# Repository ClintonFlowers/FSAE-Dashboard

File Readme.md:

# KSU Motorsports Dashboard & Data Logger

This is a custom dashboard / shift-light module created for the Kennesaw State University Motorsports student-built race car, the KS-2.
In a 5" x 1.25" x 0.5" footprint, it has:

* 20 individually-addressable RGB LED's (Neopixels)
* 3 14-segment alphanumeric LED elements for string output via scrolling text
* CAN bus communication with solderable termination jumper
* Onboard 12V to 5V switching converter plus overvoltage, transient, overcurrent, and reverse-voltage protection (i.e., Partially Student Resistant)
* A 9-DOF (accelerometer/gyro/magnetometer) inertial measurement unit with integrated sensor fusion
* A battery-backed Realtime Clock
* A Micro SD Card slot
* A 5-way Tactile Switch/Joystick
* Expansion capability via a 0.1" header at the bottom left, designed for a 16x2 character matrix or any I2C device

It's based on a combination of a Atmega328P (Arduino Uno) and a Atmega2560 (Arduino Mega) to ensure team members can program it into the future.

I've included a PDF to view the schematic without EagleCAD, and the models (STL/SLDPRT) of the enclosure pieces. The version 1 faceplate and backplate were designed for Formlabs clear resin, as the backplate's integrated cable-tie strain-relief loops may break more easily on FDM prints (due to Z-axis layer adhesion). Newer designs (version 2+) use a thin waterjet polycarbonate faceplate for simplicity.

Feel free to contact me with any questions,

Clinton Flowers

clintonflowers222@gmail.com

   Copyright 2017 Clinton Flowers

   Licensed under the Apache License, Version 2.0 (the "License");
   you may not use this file except in compliance with the License.
   You may obtain a copy of the License at

       http://www.apache.org/licenses/LICENSE-2.0

   Unless required by applicable law or agreed to in writing, software
   distributed under the License is distributed on an "AS IS" BASIS,
   WITHOUT WARRANTIES OR CONDITIONS OF ANY KIND, either express or implied.
   See the License for the specific language governing permissions and
   limitations under the License.

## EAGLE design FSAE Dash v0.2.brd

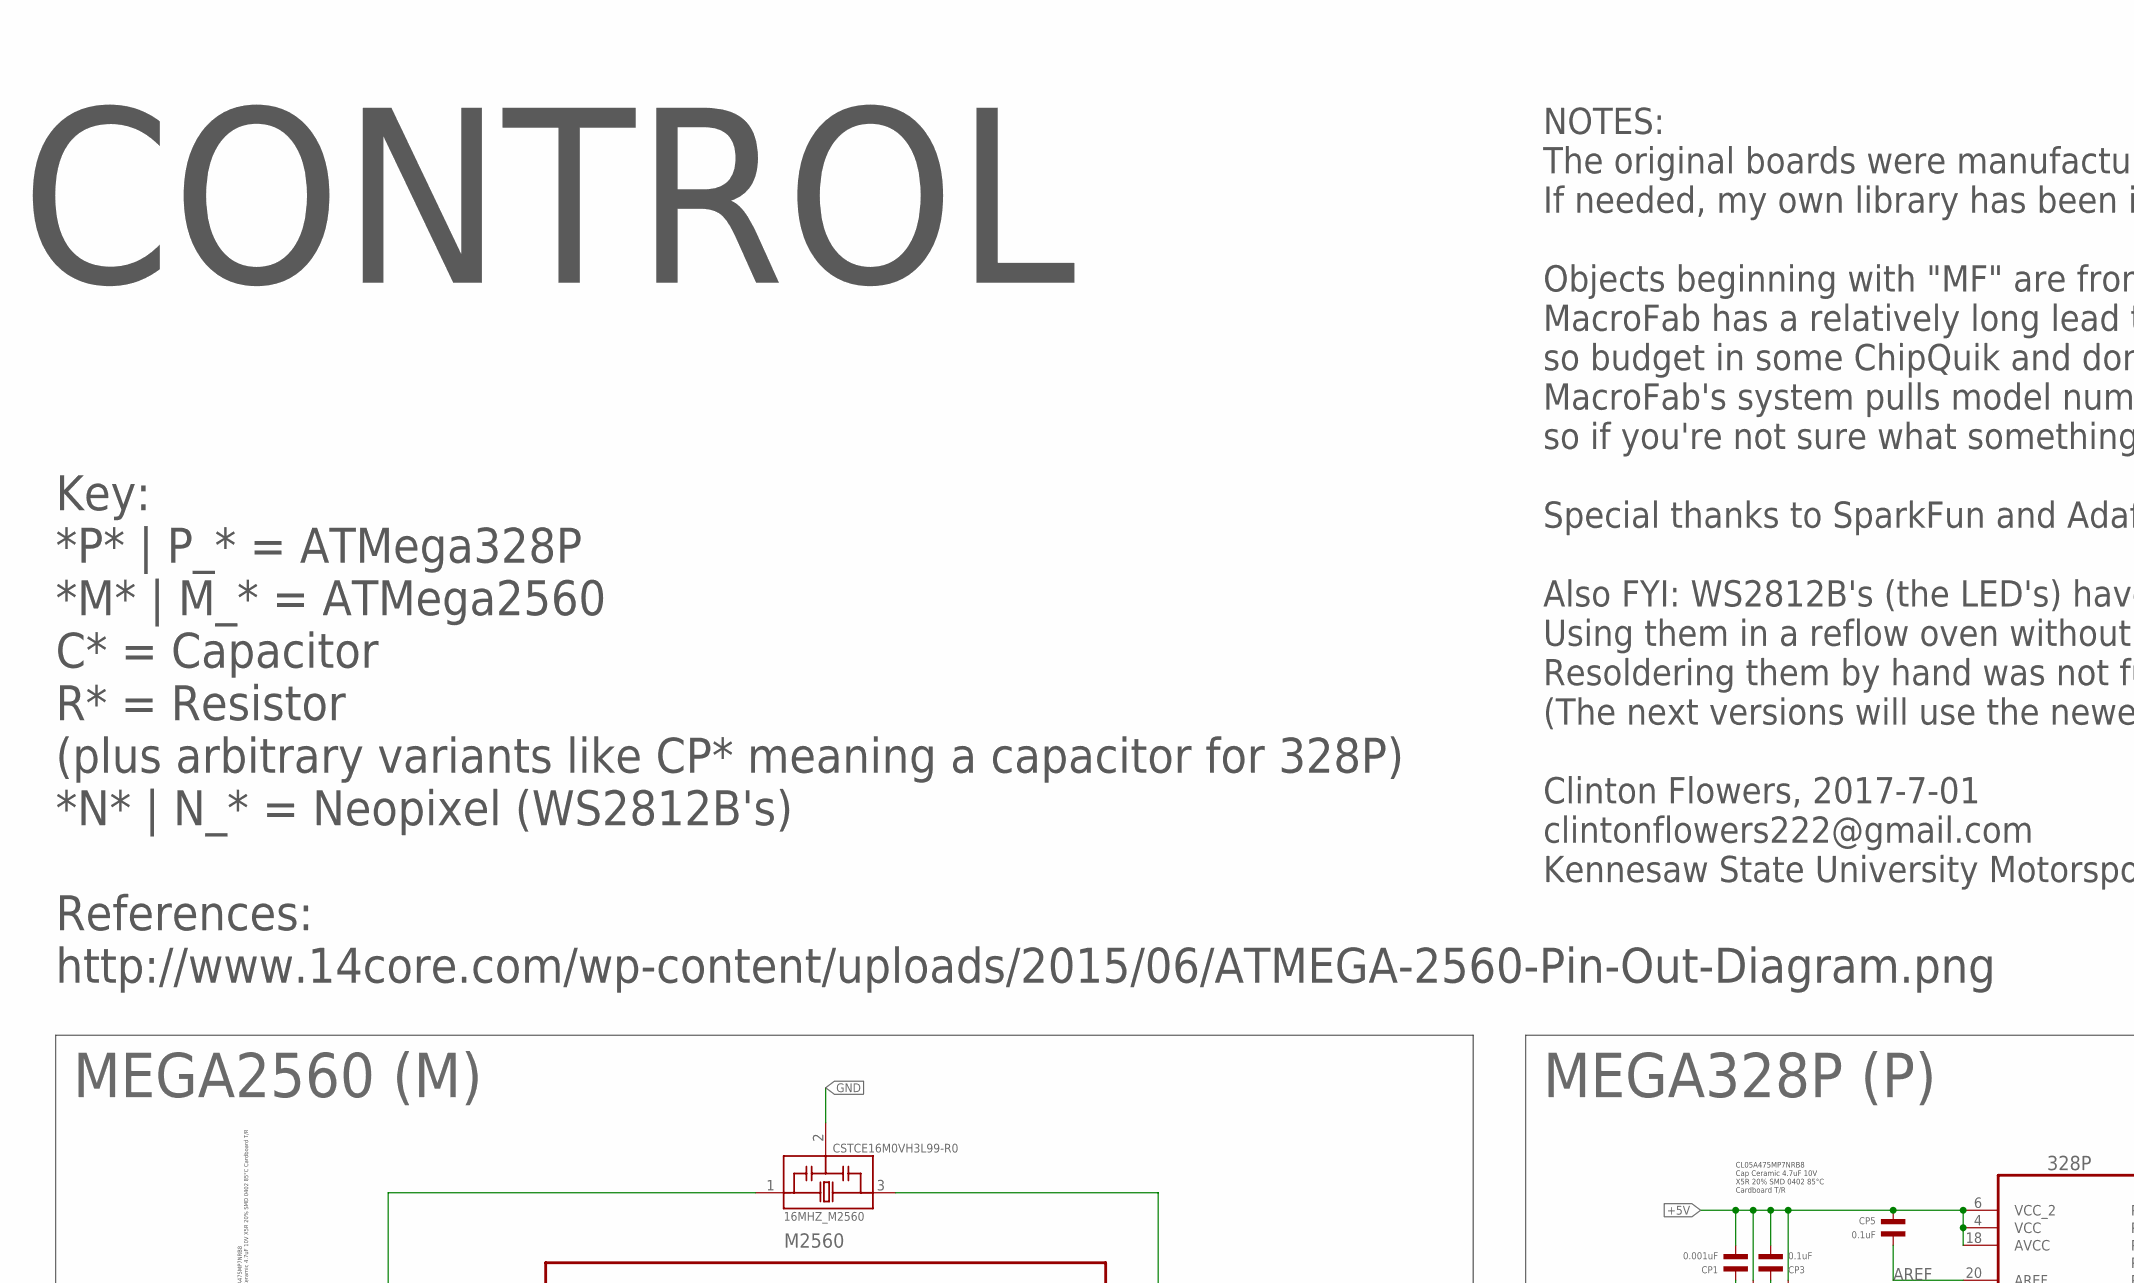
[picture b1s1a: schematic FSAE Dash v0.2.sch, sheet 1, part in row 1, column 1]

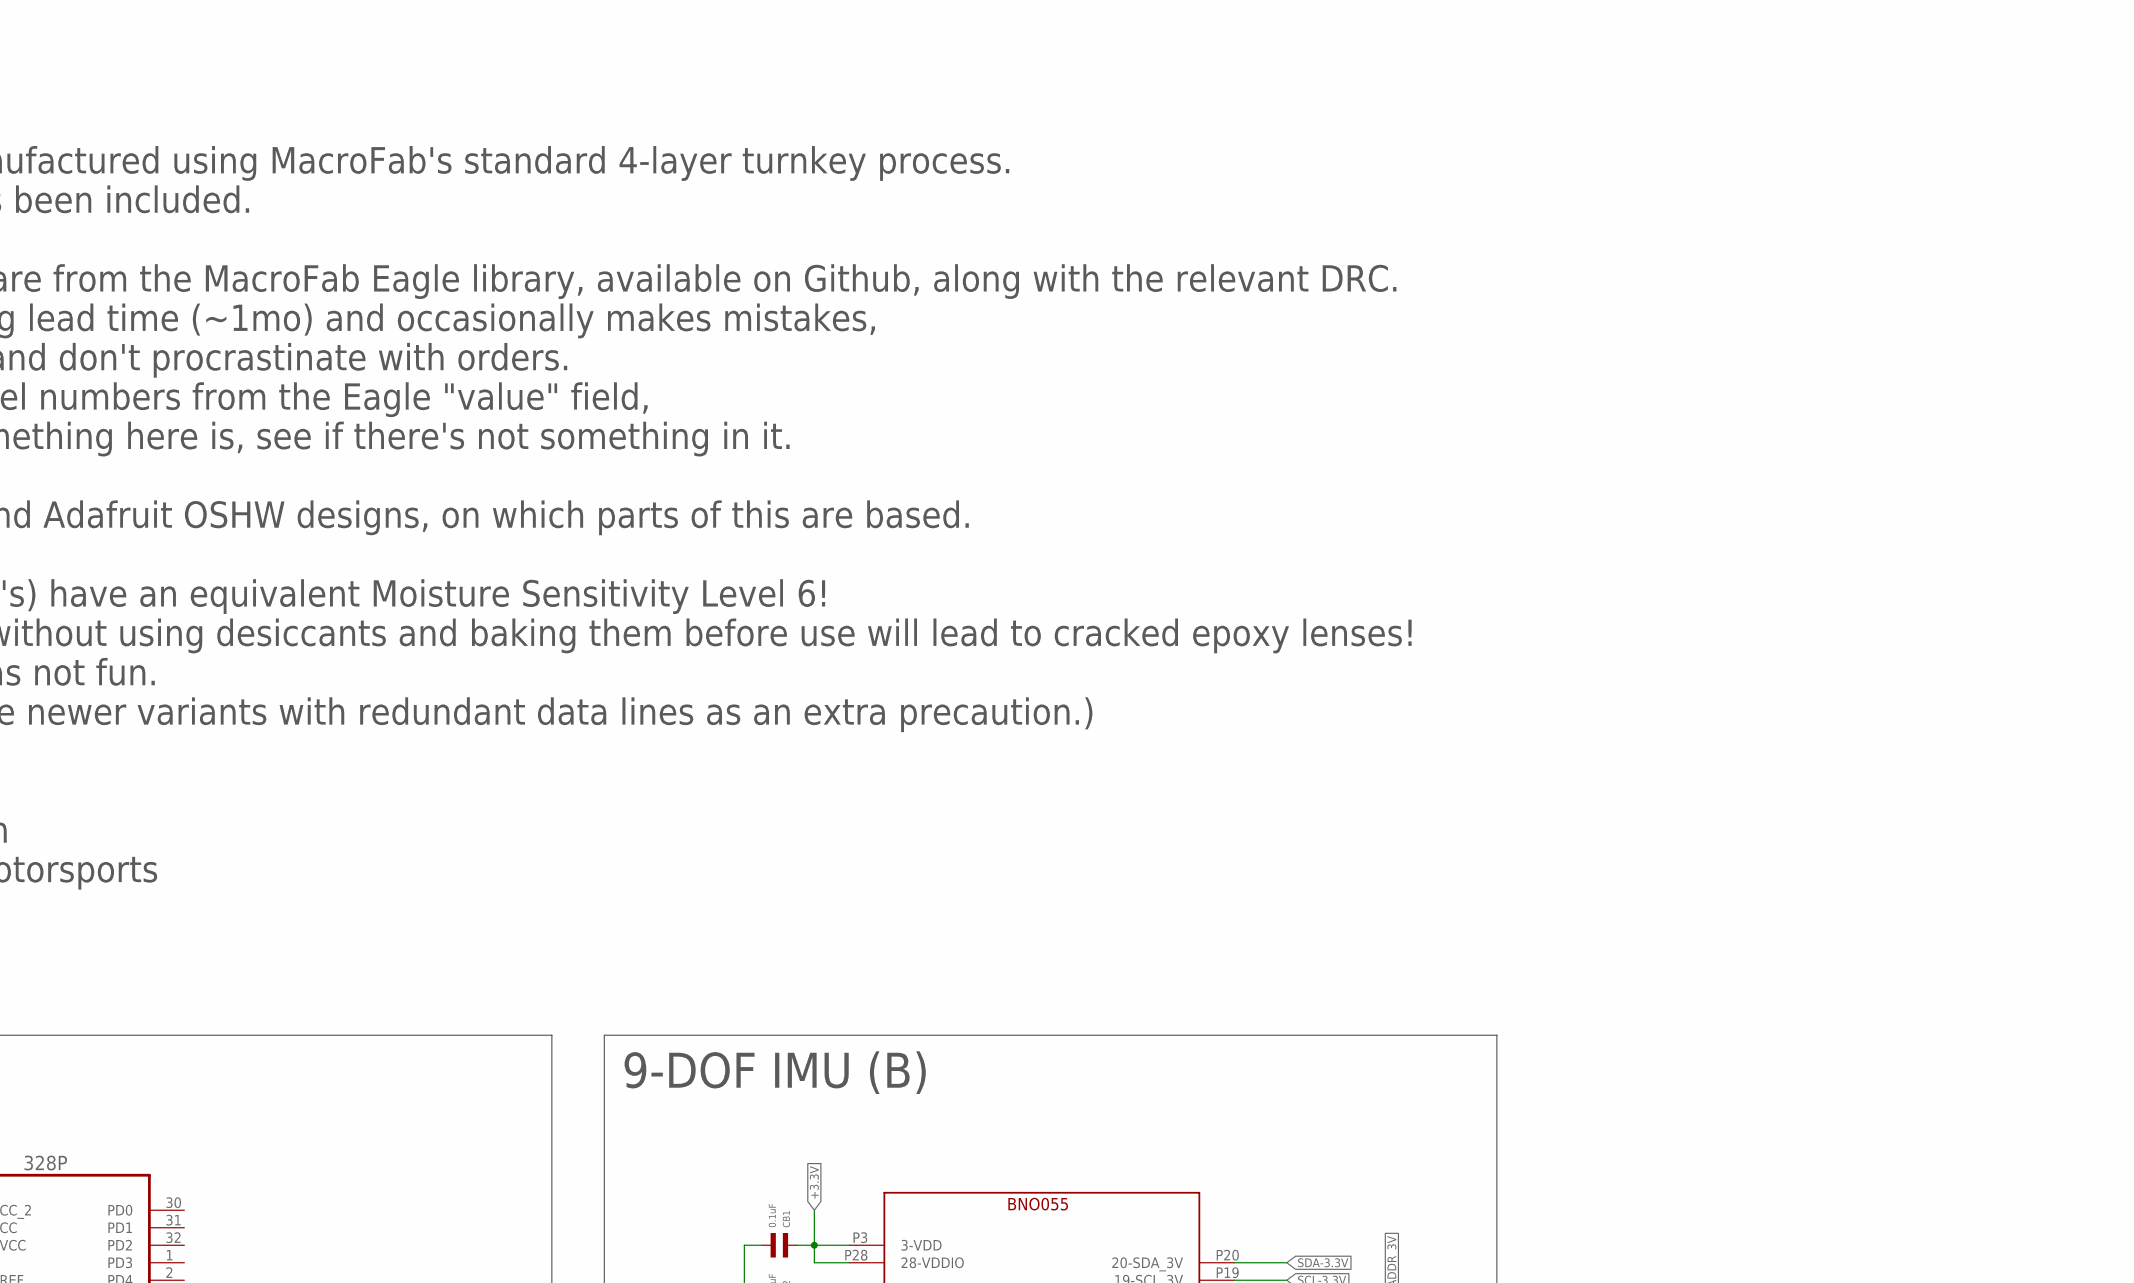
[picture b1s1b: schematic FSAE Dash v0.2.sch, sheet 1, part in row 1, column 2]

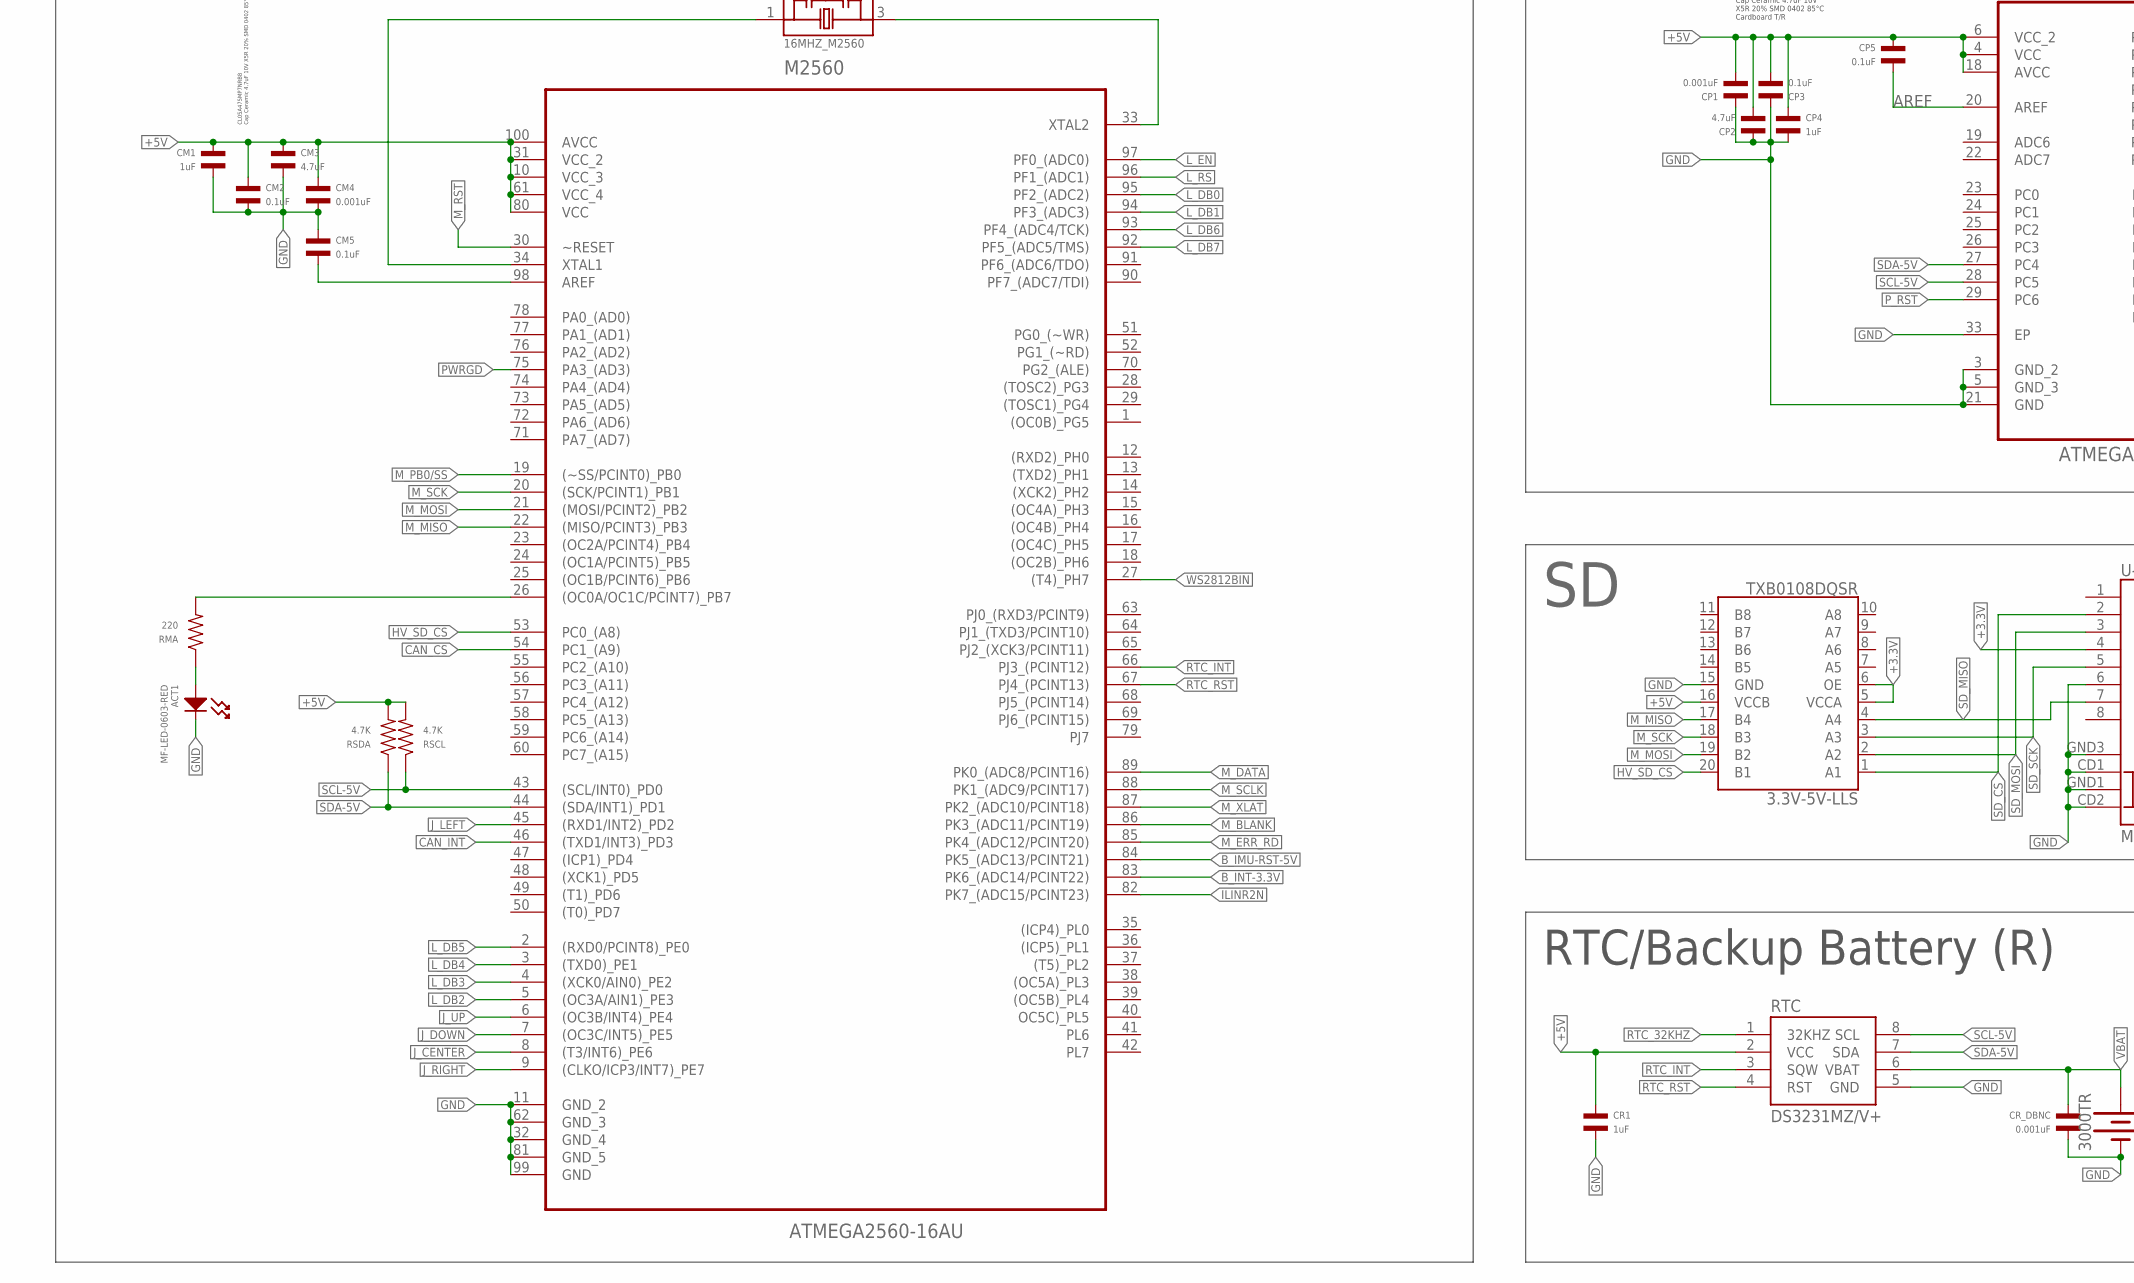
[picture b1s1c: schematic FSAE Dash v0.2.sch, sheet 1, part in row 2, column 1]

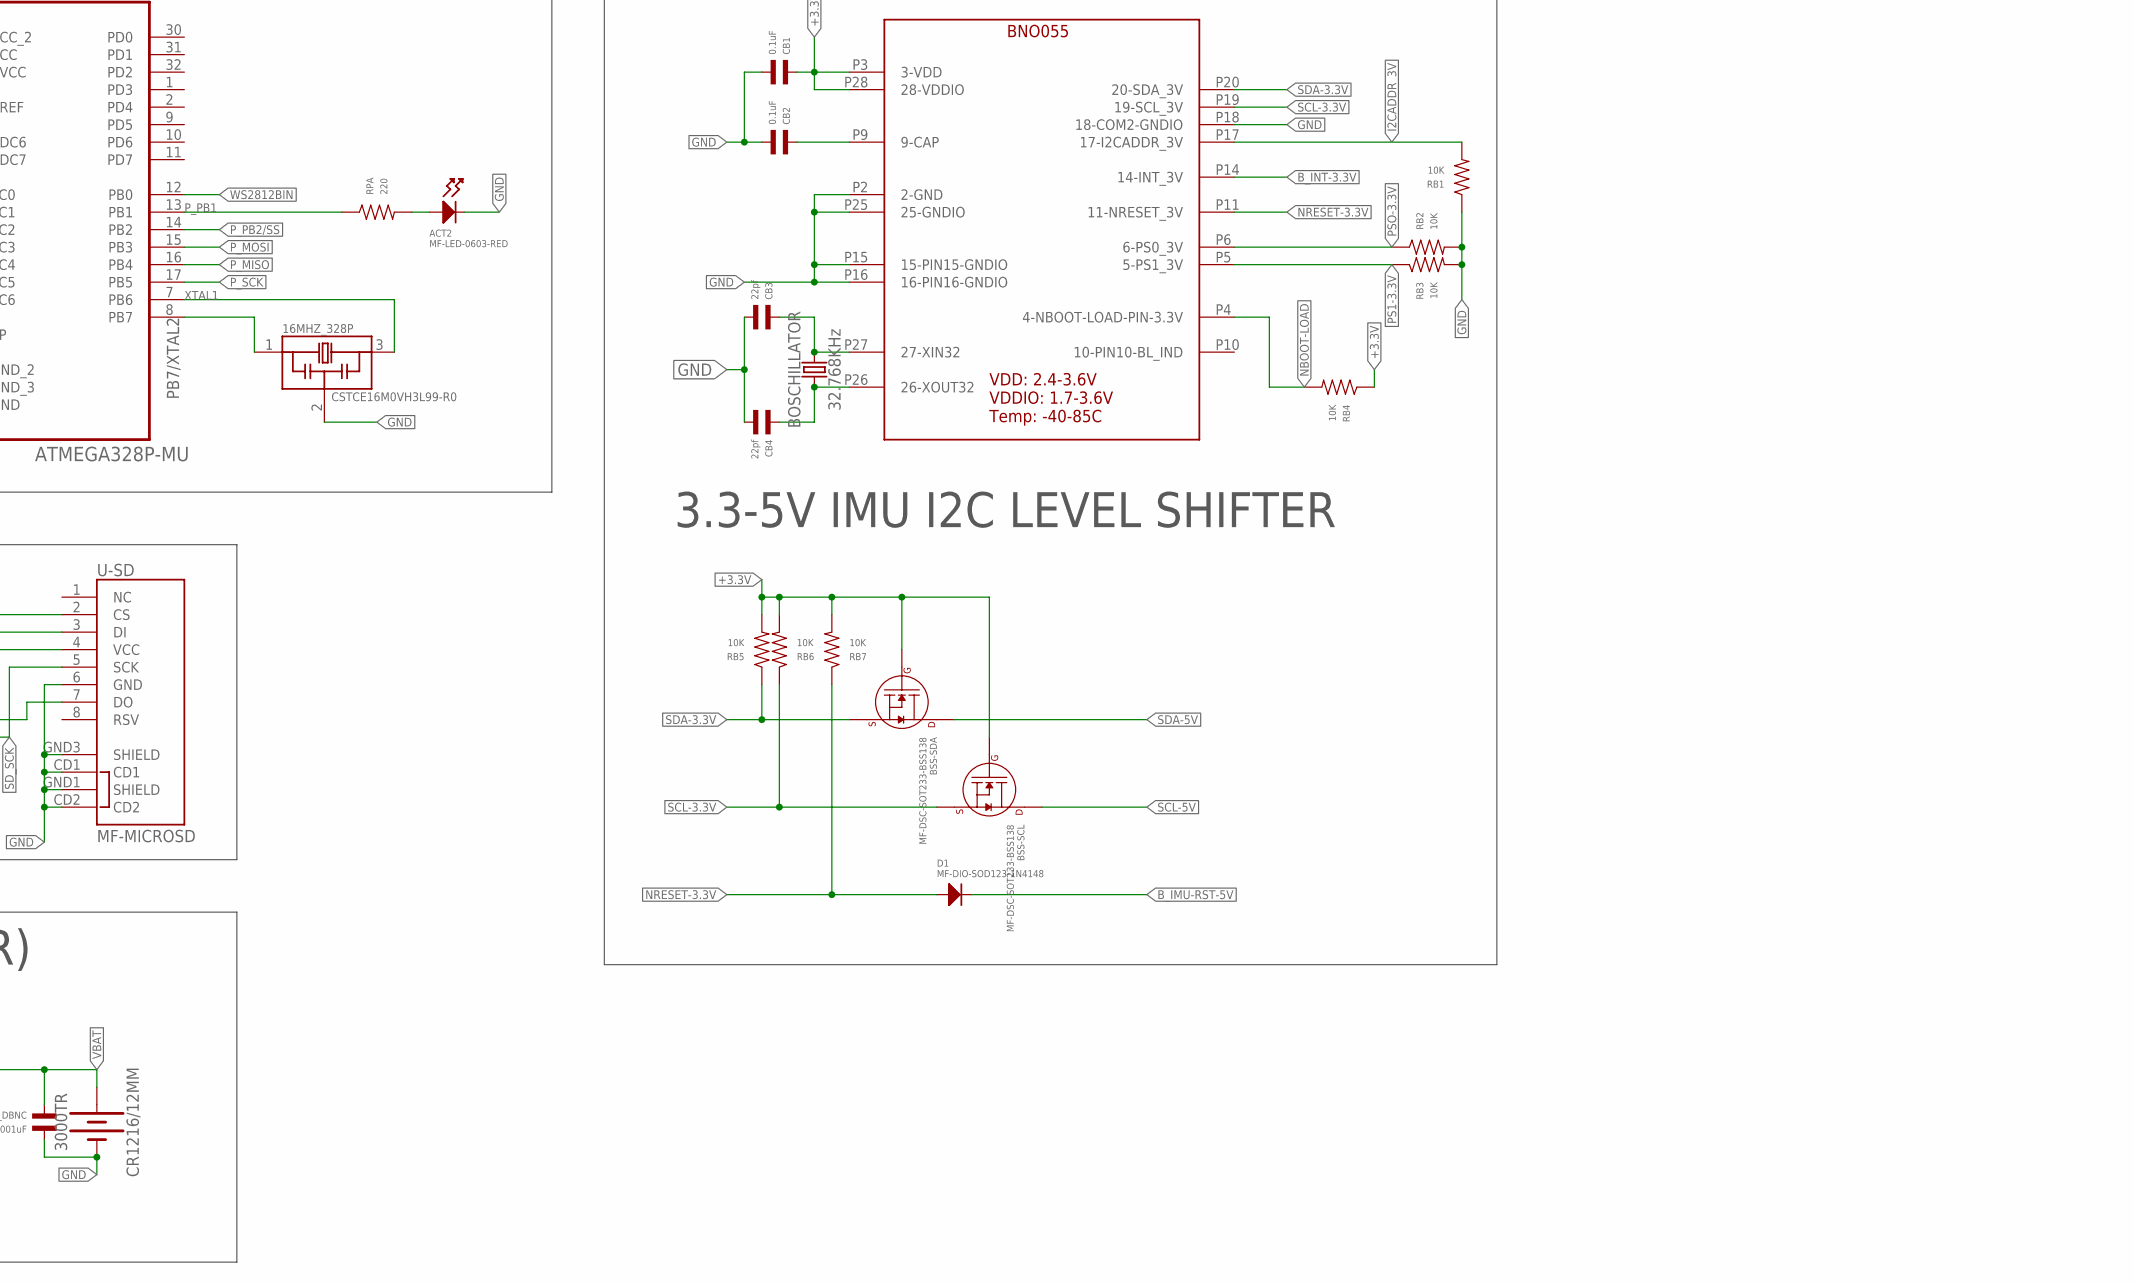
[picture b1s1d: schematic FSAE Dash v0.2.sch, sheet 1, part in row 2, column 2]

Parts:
3.3V-5V-LLS: TXB0108DQSR; UFDFN-20
16MHZ_328P, 16MHZ_M2560: CSTCE16M0VH3L99-R0; OSC_CSTCE16M0V53-R0
328P: ATMEGA328P-MU; QFN50P500X500X100-33N
ACT1, ACT2: MF-LED-0603-RED; LED0603
BNO: BNO055; BOSCH-BNO055
BOSCHILLATOR: 32.768KHz; CRYSTAL-SMD-3.2X1.5MM
BSS-SCL: MF-DSC-SOT233-BSS138; SOT-23-3
BSS-SDA: MF-DSC-SOT233-BSS138; SOT-23-3
CB1, CB2: 0.1uF; C0402
CB3, CB4: 22pf; C0402
CM1: 1uF; C0402
CM2, CM5: 0.1uF; C0402
CM3: 4.7uF; C0402
CM4: 0.001uF; C0402
CP1: 0.001uF; C0402
CP2: 4.7uF; C0402
CP3, CP5: 0.1uF; C0402
CP4: 1uF; C0402
CR1: 1uF; C0402
CR1216/12MM: 3000TR; BATTCON_12MM
CR_DBNC: 0.001uF; C0402
D1: MF-DIO-SOD123-1N4148; SOD-123
M2560: ATMEGA2560-16AU; QFP50P1600X1600X120-100N
RB1, RB2, RB3, RB4, RB5, RB6, RB7: 10K; R0402
RMA: 220; R0402
RPA: 220; R0402
RSCL: 4.7K; R0402
RSDA: 4.7K; R0402
RTC: DS3231MZ/V+; SO08
U-SD: MF-MICROSD; MICROSD_1:1

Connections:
+3.3V: 3.3V-5V-LLS.5 (VCCA), 3.3V-5V-LLS.6 (OE), BNO.P3 (3-VDD), BNO.P28 (28-VDDIO), BSS-SCL.P$1 (GATE), BSS-SDA.P$1 (GATE), CB1.P$1, RB4.P$1, RB5.P$2, RB6.P$2, RB7.P$2, U-SD.4 (VCC); also elsewhere on the board
+5V: 3.3V-5V-LLS.16 (VCCB), 328P.4 (VCC), 328P.6 (VCC_2), 328P.18 (AVCC), CM1.P$1, CM2.P$1, CM3.P$1, CM4.P$1, CP1.P$2, CP2.P$2, CP3.P$2, CP4.P$1, CP5.P$1, CR1.P$1, M2560.10 (VCC_3), M2560.31 (VCC_2), M2560.61 (VCC_4), M2560.80 (VCC), M2560.100 (AVCC), RSCL.P$2, RSDA.P$2, RTC.2 (VCC); also elsewhere on the board
AREF: 328P.20 (AREF), CP5.P$2
BCAP: BNO.P9 (9-CAP), CB2.P$1
B_IMU-RST-5V: D1.CATHODE, M2560.84 (PK5_(ADC13/PCINT21))
B_INT-3.3V: BNO.P14 (14-INT_3V), M2560.83 (PK6_(ADC14/PCINT22))
CAN_CS: M2560.54 (PC1_(A9)); also elsewhere on the board
CAN_INT: M2560.46 ((TXD1/INT3)_PD3); also elsewhere on the board
GND: 3.3V-5V-LLS.15 (GND), 16MHZ_328P.2, 16MHZ_M2560.2, 328P.3 (GND_2), 328P.5 (GND_3), 328P.21 (GND), 328P.33 (EP), ACT1.CATHODE, ACT2.CATHODE, BNO.P2 (2-GND), BNO.P15 (15-PIN15-GNDIO), BNO.P16 (16-PIN16-GNDIO), BNO.P18 (18-COM2-GNDIO), BNO.P25 (25-GNDIO), CB1.P$2, CB2.P$2, CB3.P$2, CB4.P$2, CM1.P$2, CM2.P$2, CM3.P$2, CM4.P$2, CM5.P$1, CP1.P$1, CP2.P$1, CP3.P$1, CP4.P$2, CR1.P$2, CR1216/12MM.GND (-), CR_DBNC.P$2, M2560.11 (GND_2), M2560.32 (GND_4), M2560.62 (GND_3), M2560.81 (GND_5), M2560.99 (GND), RB1.P$1, RB2.P$2, RB3.P$2, RTC.5 (GND), U-SD.6 (GND), U-SD.CD1, U-SD.CD2, U-SD.GND1 (SHIELD), U-SD.GND3 (SHIELD); also elsewhere on the board
HV_SD_CS: 3.3V-5V-LLS.20 (B1), M2560.53 (PC0_(A8))
I2CADDR_3V: BNO.P17 (17-I2CADDR_3V), RB1.P$2
ILINR2N: M2560.82 (PK7_(ADC15/PCINT23)); also elsewhere on the board
J_CENTER: M2560.8 ((T3/INT6)_PE6); also elsewhere on the board
J_DOWN: M2560.7 ((OC3C/INT5)_PE5); also elsewhere on the board
J_LEFT: M2560.45 ((RXD1/INT2)_PD2); also elsewhere on the board
J_RIGHT: M2560.9 ((CLKO/ICP3/INT7)_PE7); also elsewhere on the board
J_UP: M2560.6 ((OC3B/INT4)_PE4); also elsewhere on the board
L_DB0: M2560.95 (PF2_(ADC2)); also elsewhere on the board
L_DB1: M2560.94 (PF3_(ADC3)); also elsewhere on the board
L_DB2: M2560.5 ((OC3A/AIN1)_PE3); also elsewhere on the board
L_DB3: M2560.4 ((XCK0/AIN0)_PE2); also elsewhere on the board
L_DB4: M2560.3 ((TXD0)_PE1); also elsewhere on the board
L_DB5: M2560.2 ((RXD0/PCINT8)_PE0); also elsewhere on the board
L_DB6: M2560.93 (PF4_(ADC4/TCK)); also elsewhere on the board
L_DB7: M2560.92 (PF5_(ADC5/TMS)); also elsewhere on the board
L_EN: M2560.97 (PF0_(ADC0)); also elsewhere on the board
L_RS: M2560.96 (PF1_(ADC1)); also elsewhere on the board
M_BLANK: M2560.86 (PK3_(ADC11/PCINT19)); also elsewhere on the board
M_DATA: M2560.89 (PK0_(ADC8/PCINT16)); also elsewhere on the board
M_ERR_RD: M2560.85 (PK4_(ADC12/PCINT20)); also elsewhere on the board
M_MISO: 3.3V-5V-LLS.17 (B4), M2560.22 ((MISO/PCINT3)_PB3); also elsewhere on the board
M_MOSI: 3.3V-5V-LLS.19 (B2), M2560.21 ((MOSI/PCINT2)_PB2); also elsewhere on the board
M_PB0/SS: M2560.19 ((~SS/PCINT0)_PB0)
M_RST: M2560.30 (~RESET); also elsewhere on the board
M_SCK: 3.3V-5V-LLS.18 (B3), M2560.20 ((SCK/PCINT1)_PB1); also elsewhere on the board
M_SCLK: M2560.88 (PK1_(ADC9/PCINT17)); also elsewhere on the board
M_XLAT: M2560.87 (PK2_(ADC10/PCINT18)); also elsewhere on the board
unnamed: ACT2.ANODE, RPA.P$2
unnamed: 16MHZ_M2560.3, M2560.33 (XTAL2)
unnamed: CM5.P$2, M2560.98 (AREF)
unnamed: 16MHZ_M2560.1, M2560.34 (XTAL1)
unnamed: ACT1.ANODE, RMA.P$1
unnamed: BNO.P26 (26-XOUT32), BOSCHILLATOR.P$1 (1), CB4.P$1
unnamed: BNO.P27 (27-XIN32), BOSCHILLATOR.P$2 (2), CB3.P$1
unnamed: M2560.26 ((OC0A/OC1C/PCINT7)_PB7), RMA.P$2
NBOOT-LOAD: BNO.P4 (4-NBOOT-LOAD-PIN-3.3V), RB4.P$2
NRESET-3.3V: BNO.P11 (11-NRESET_3V), D1.ANODE, RB7.P$1
PB7/XTAL2: 16MHZ_328P.1, 328P.8 (PB7)
PS1-3.3V: BNO.P5 (5-PS1_3V), RB3.P$1
PSO-3.3V: BNO.P6 (6-PS0_3V), RB2.P$1
PWRGD: M2560.75 (PA3_(AD3)); also elsewhere on the board
P_MISO: 328P.16 (PB4); also elsewhere on the board
P_MOSI: 328P.15 (PB3); also elsewhere on the board
P_PB1: 328P.13 (PB1), RPA.P$1
P_PB2/SS: 328P.14 (PB2)
P_RST: 328P.29 (PC6); also elsewhere on the board
P_SCK: 328P.17 (PB5); also elsewhere on the board
RTC_32KHZ: RTC.1 (32KHZ)
RTC_INT: M2560.66 (PJ3_(PCINT12)), RTC.3 (SQW)
RTC_RST: M2560.67 (PJ4_(PCINT13)), RTC.4 (RST)
SCL-3.3V: BNO.P19 (19-SCL_3V), BSS-SCL.P$2 (SOURCE), RB6.P$1
SCL-5V: 328P.28 (PC5), BSS-SCL.P$3 (DRAIN), M2560.43 ((SCL/INT0)_PD0), RSCL.P$1, RTC.8 (SCL); also elsewhere on the board
SDA-3.3V: BNO.P20 (20-SDA_3V), BSS-SDA.P$2 (SOURCE), RB5.P$1
SDA-5V: 328P.27 (PC4), BSS-SDA.P$3 (DRAIN), M2560.44 ((SDA/INT1)_PD1), RSDA.P$1, RTC.7 (SDA); also elsewhere on the board
SD_CS: 3.3V-5V-LLS.1 (A1), U-SD.2 (CS)
SD_MISO: 3.3V-5V-LLS.4 (A4), U-SD.7 (DO)
SD_MOSI: 3.3V-5V-LLS.2 (A2), U-SD.3 (DI)
SD_SCK: 3.3V-5V-LLS.3 (A3), U-SD.5 (SCK)
VBAT: CR1216/12MM.PWR@1 (+), CR_DBNC.P$1, RTC.6 (VBAT)
WS2812BIN: 328P.12 (PB0), M2560.27 ((T4)_PH7); also elsewhere on the board
XTAL1: 16MHZ_328P.3, 328P.7 (PB6)

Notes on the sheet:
MEGA2560 (M)
MEGA328P (P)
CL05A475MP7NRB8 Cap Ceramic 4.7uF 10V X5R 20% SMD 0402 85°C Cardboard T/R
CL05A475MP7NRB8 Cap Ceramic 4.7uF 10V X5R 20% SMD 0402 85°C Cardboard T/R
Key: *P* | P_* = ATMega328P *M* | M_* = ATMega2560 C* = Capacitor R* = Resistor (plus arbitrary variants like CP* meaning a capacitor for 328P) *N* | N_* = Neopixel (WS2812B's) References: http://www.14core.com/wp-content/uploads/2015/06/ATMEGA-2560-Pin-Out-Diagram.png
CONTROL
9-DOF IMU (B)
3.3-5V IMU I2C LEVEL SHIFTER
RTC/Backup Battery (R)
NOTES: The original boards were manufactured using MacroFab's standard 4-layer turnkey process. If needed, my own library has been included. Objects beginning with "MF" are from the MacroFab Eagle library, available on Github, along with the relevant DRC. MacroFab has a relatively long lead time (~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

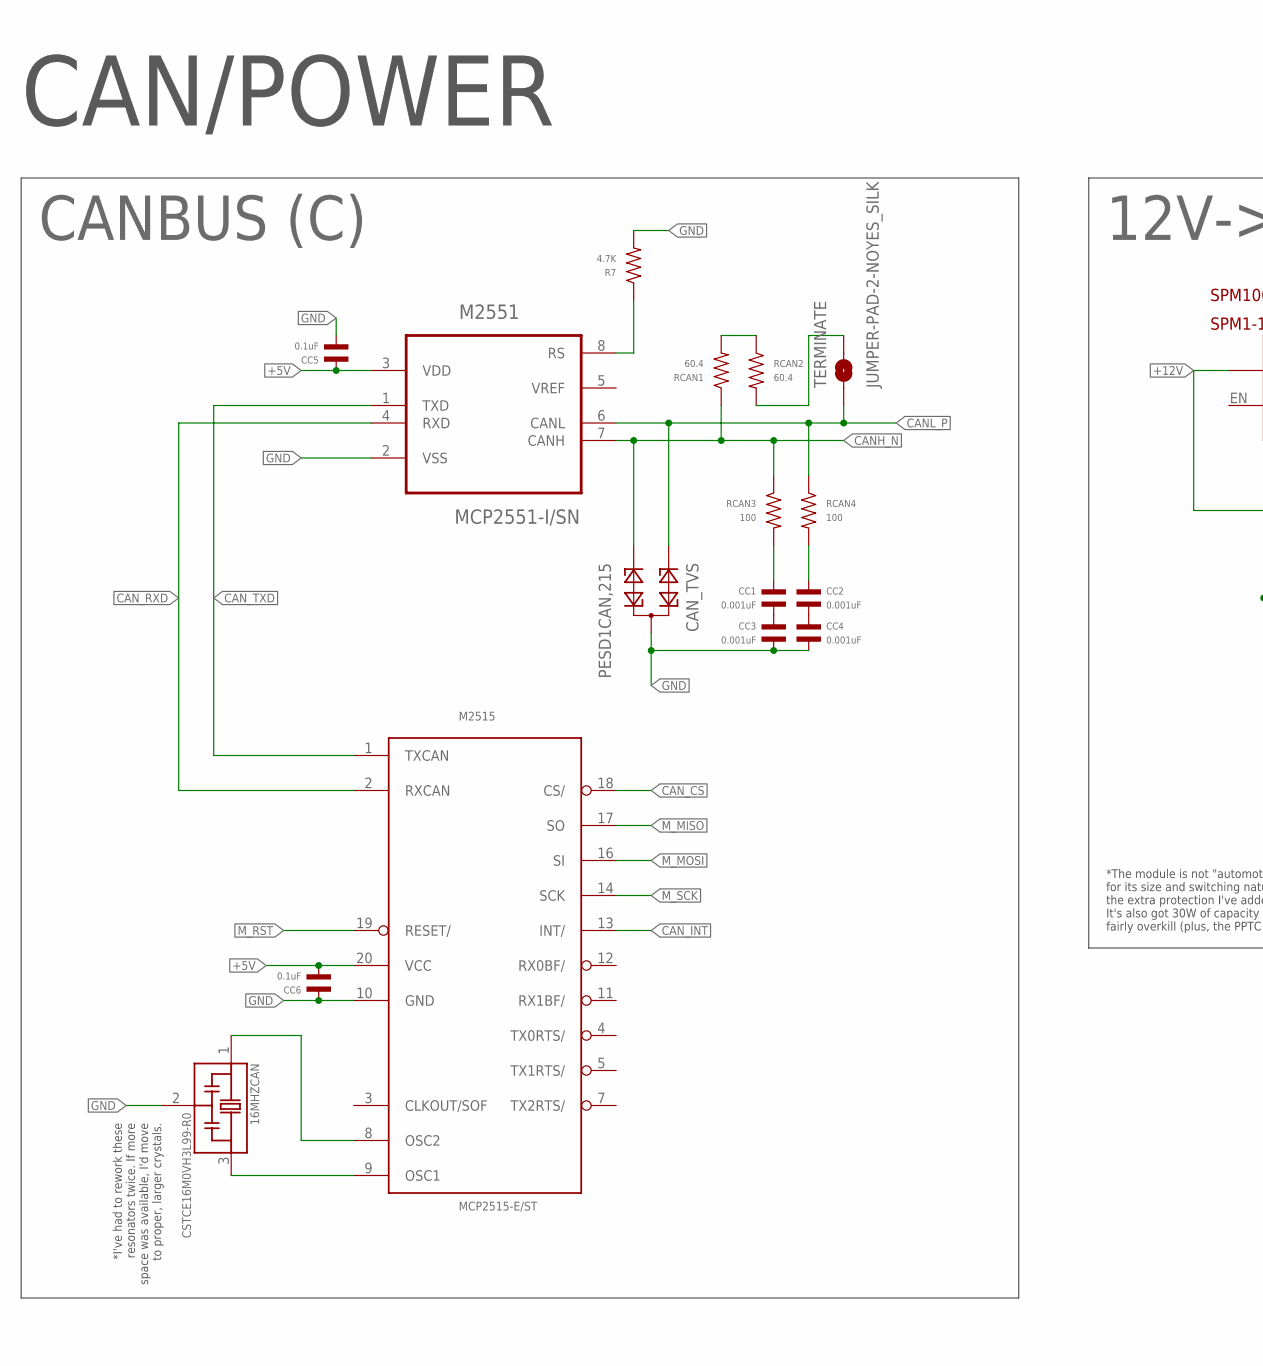
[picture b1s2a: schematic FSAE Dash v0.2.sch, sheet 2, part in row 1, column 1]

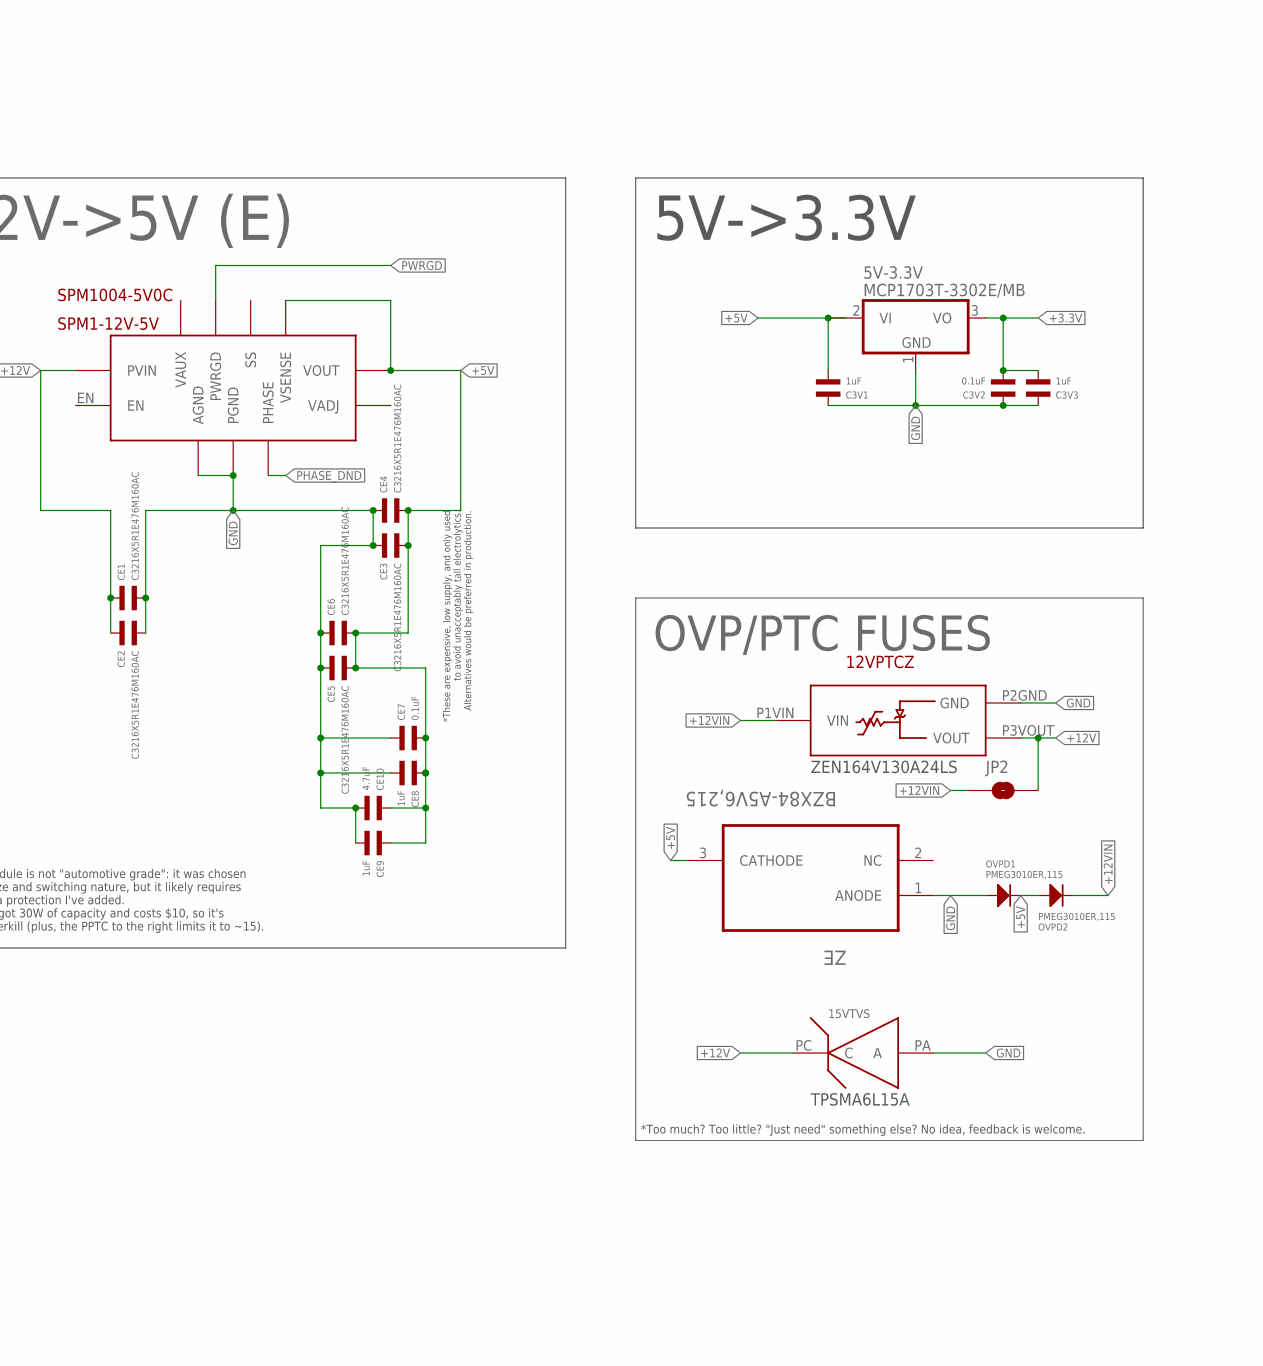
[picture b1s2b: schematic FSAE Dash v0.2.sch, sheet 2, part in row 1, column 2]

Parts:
5V-3.3V: MCP1703T-3302E/MB; SOT89
12VPTCZ: ZEN164V130A24LS; LITTELFUSE-POLYZEN-ZEN164V130A24LS
15VTVS: TPSMA6L15A; LITTELFUSE-TPSMA6L15A
16MHZCAN: CSTCE16M0VH3L99-R0; OSC_CSTCE16M0V53-R0
C3V1, C3V3: 1uF; C0402
C3V2: 0.1uF; C0402
CAN_TVS: PESD1CAN,215; SOT23
CC1, CC2, CC3, CC4: 0.001uF; C0402
CC5, CC6: 0.1uF; C0402
CE1, CE2, CE3, CE4, CE5, CE6: C3216X5R1E476M160AC; C1206
CE7: 0.1uF; C0402
CE8, CE9: 1uF; C0402
CE10: 4.7uF; C0402
JP2: JUMPER-SMT_2_NO_SILK; SMT-JUMPER_2_NO_SILK
M2515: MCP2515-E/ST; TSSOP20
M2551: MCP2551-I/SN; SOIC127P600X175-8N
OVPD1, OVPD2: PMEG3010ER,115; SOD-123
R7: 4.7K; R0402
RCAN1, RCAN2: 60.4; R0402
RCAN3, RCAN4: 100; R0402
SPM1-12V-5V: SPM1004-5V0C
TERMINATE: JUMPER-PAD-2-NOYES_SILK; PAD-JUMPER-2-NO_YES_SILK
ZE: BZX84-A5V6,215; SOT91P240X110-3N

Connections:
+3.3V: 5V-3.3V.3 (VO), C3V2.P$2, C3V3.P$2; also elsewhere on the board
+5V: 5V-3.3V.2 (VI), 5V-3.3V.2@1 (VI1), C3V1.P$2, CC5.P$1, CC6.P$2, CE3.P$2, CE4.P$2, CE5.P$2, CE6.P$2, CE7.P$2, CE8.P$1, CE9.P$1, CE10.P$1, M2515.20 (VCC), M2551.3 (VDD), OVPD1.CATHODE, OVPD2.ANODE, SPM1-12V-5V.VOUT$1 (VOUT), SPM1-12V-5V.VOUT$2 (VOUT), SPM1-12V-5V.VOUT$3 (VOUT), SPM1-12V-5V.VOUT$4 (VOUT), SPM1-12V-5V.VOUT$5 (VOUT), SPM1-12V-5V.VOUT$6 (VOUT), SPM1-12V-5V.VOUT$7 (VOUT), SPM1-12V-5V.VOUT$8 (VOUT), SPM1-12V-5V.VOUT$9 (VOUT), SPM1-12V-5V.VOUT$10 (VOUT), SPM1-12V-5V.VOUT$11 (VOUT), SPM1-12V-5V.VOUT$12 (VOUT), SPM1-12V-5V.VOUT$13 (VOUT), SPM1-12V-5V.VOUT$14 (VOUT), SPM1-12V-5V.VOUT$15 (VOUT), SPM1-12V-5V.VOUT$16 (VOUT), SPM1-12V-5V.VOUT$17 (VOUT), SPM1-12V-5V.VOUT$18 (VOUT), SPM1-12V-5V.VSENSE, ZE.3 (CATHODE); also elsewhere on the board
+12V: 12VPTCZ.P3VOUT (VOUT), 15VTVS.PC (C), CE1.P$1, CE2.P$1, JP2.2, SPM1-12V-5V.PVIN$1 (PVIN), SPM1-12V-5V.PVIN$2 (PVIN), SPM1-12V-5V.PVIN$3 (PVIN), SPM1-12V-5V.PVIN$4 (PVIN), SPM1-12V-5V.PVIN$5 (PVIN), SPM1-12V-5V.PVIN$6 (PVIN), SPM1-12V-5V.PVIN$7 (PVIN), SPM1-12V-5V.PVIN$8 (PVIN)
+12VIN: 12VPTCZ.P1VIN (VIN), JP2.1, OVPD2.CATHODE; also elsewhere on the board
CANH_N: CAN_TVS.2, M2551.7 (CANH), RCAN1.P$1, RCAN3.P$1; also elsewhere on the board
CANL_P: CAN_TVS.1, M2551.6 (CANL), RCAN4.P$1, TERMINATE.1; also elsewhere on the board
CAN_CS: M2515.18 (CS/); also elsewhere on the board
CAN_INT: M2515.13 (INT/); also elsewhere on the board
CAN_RXD: M2515.2 (RXCAN), M2551.4 (RXD)
CAN_TXD: M2515.1 (TXCAN), M2551.1 (TXD)
GND: 5V-3.3V.1 (GND), 12VPTCZ.P2GND (GND), 15VTVS.PA (A), 16MHZCAN.2, C3V1.P$1, C3V2.P$1, C3V3.P$1, CAN_TVS.3, CC3.P$2, CC4.P$2, CC5.P$2, CC6.P$1, CE1.P$2, CE2.P$2, CE3.P$1, CE4.P$1, CE5.P$1, CE6.P$1, CE7.P$1, CE8.P$2, CE9.P$2, CE10.P$2, M2515.10 (GND), M2551.2 (VSS), OVPD1.ANODE, R7.P$2, SPM1-12V-5V.AGND$1 (AGND), SPM1-12V-5V.AGND$2 (AGND), SPM1-12V-5V.AGND$3 (AGND), SPM1-12V-5V.PGND$1 (PGND), SPM1-12V-5V.PGND$2 (PGND), SPM1-12V-5V.PGND$3 (PGND), SPM1-12V-5V.PGND$4 (PGND), SPM1-12V-5V.PGND$5 (PGND), SPM1-12V-5V.PGND$6 (PGND), SPM1-12V-5V.PGND$7 (PGND), SPM1-12V-5V.PGND$8 (PGND), SPM1-12V-5V.PGND$9 (PGND), SPM1-12V-5V.PGND$10 (PGND), SPM1-12V-5V.PGND$11 (PGND), SPM1-12V-5V.PGND$12 (PGND), SPM1-12V-5V.PGND$13 (PGND), SPM1-12V-5V.PGND$14 (PGND), SPM1-12V-5V.PGND$15 (PGND), SPM1-12V-5V.PGND$16 (PGND), SPM1-12V-5V.PGND$17 (PGND), SPM1-12V-5V.PGND$18 (PGND), SPM1-12V-5V.PGND$19 (PGND), SPM1-12V-5V.PGND$20 (PGND), SPM1-12V-5V.PGND$21 (PGND), SPM1-12V-5V.PGND$22 (PGND), SPM1-12V-5V.PGND$23 (PGND), SPM1-12V-5V.PGND$24 (PGND), SPM1-12V-5V.PGND$25 (PGND), SPM1-12V-5V.PGND$26 (PGND), SPM1-12V-5V.PGND$27 (PGND), SPM1-12V-5V.PGND$28 (PGND), SPM1-12V-5V.PGND$29 (PGND), SPM1-12V-5V.PGND$30 (PGND), SPM1-12V-5V.PGND$31 (PGND), SPM1-12V-5V.PGND$32 (PGND), SPM1-12V-5V.PGND$33 (PGND), SPM1-12V-5V.PGND$34 (PGND), ZE.1 (ANODE); also elsewhere on the board
M_MISO: M2515.17 (SO); also elsewhere on the board
M_MOSI: M2515.16 (SI); also elsewhere on the board
M_RST: M2515.19 (RESET/); also elsewhere on the board
M_SCK: M2515.14 (SCK); also elsewhere on the board
unnamed: CC2.P$2, CC4.P$1
unnamed: CC1.P$2, CC3.P$1
unnamed: M2551.8 (RS), R7.P$1
unnamed: 16MHZCAN.1, M2515.8 (OSC2)
unnamed: 16MHZCAN.3, M2515.9 (OSC1)
unnamed: RCAN1.P$2, RCAN2.P$1
unnamed: CC1.P$1, RCAN3.P$2
unnamed: CC2.P$1, RCAN4.P$2
unnamed: RCAN2.P$2, TERMINATE.2
PHASE_DND: SPM1-12V-5V.PHASE$1 (PHASE), SPM1-12V-5V.PHASE$2 (PHASE), SPM1-12V-5V.PHASE$3 (PHASE)
PWRGD: SPM1-12V-5V.PWRGD; also elsewhere on the board

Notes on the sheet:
CANBUS (C)
12V->5V (E)
5V->3.3V
CAN/POWER
OVP/PTC FUSES
TPSMA6L15A
ZEN164V130A24LS
*These are expensive, low supply, and only used to avoid unacceptably tall electrolytics. Alternatives would be preferred in production.
*The module is not "automotive grade": it was chosen for its size and switching nature, but it likely requires the extra protection I've added. It's also got 30W of capacity and costs $10, so it's fairly overkill (plus, the PPTC to the right limits it to ~15).
*Too much? Too little? "Just need" something else? No idea, feedback is welcome.
*I've had to rework these resonators twice. If more space was available, I'd move to proper, larger crystals.

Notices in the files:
Dash0.2_2560_Code/Dash0.2_2560_Code.ino:
MSCan_Sniffer was used and is Copyright (c) 2013 David Will - davidwill@gmail.com The MIT License (MIT)
parts and their libraries:
SparkFun-Connectors: Licensing: Creative Commons ShareAlike 4.0 International - https://creativecommons.org/licenses/by-sa/4.0
microbuilder: This work is placed in the public domain, and may be freely used for commercial and non-commercial work with the following conditions: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
